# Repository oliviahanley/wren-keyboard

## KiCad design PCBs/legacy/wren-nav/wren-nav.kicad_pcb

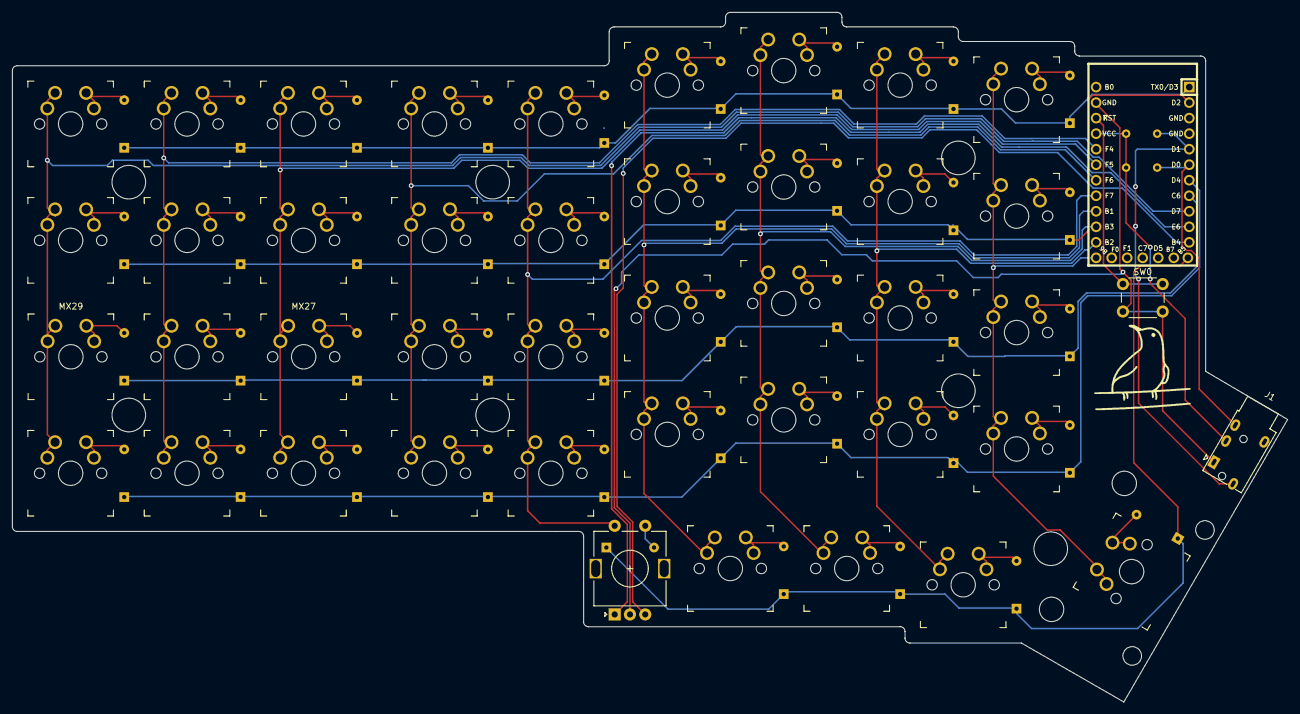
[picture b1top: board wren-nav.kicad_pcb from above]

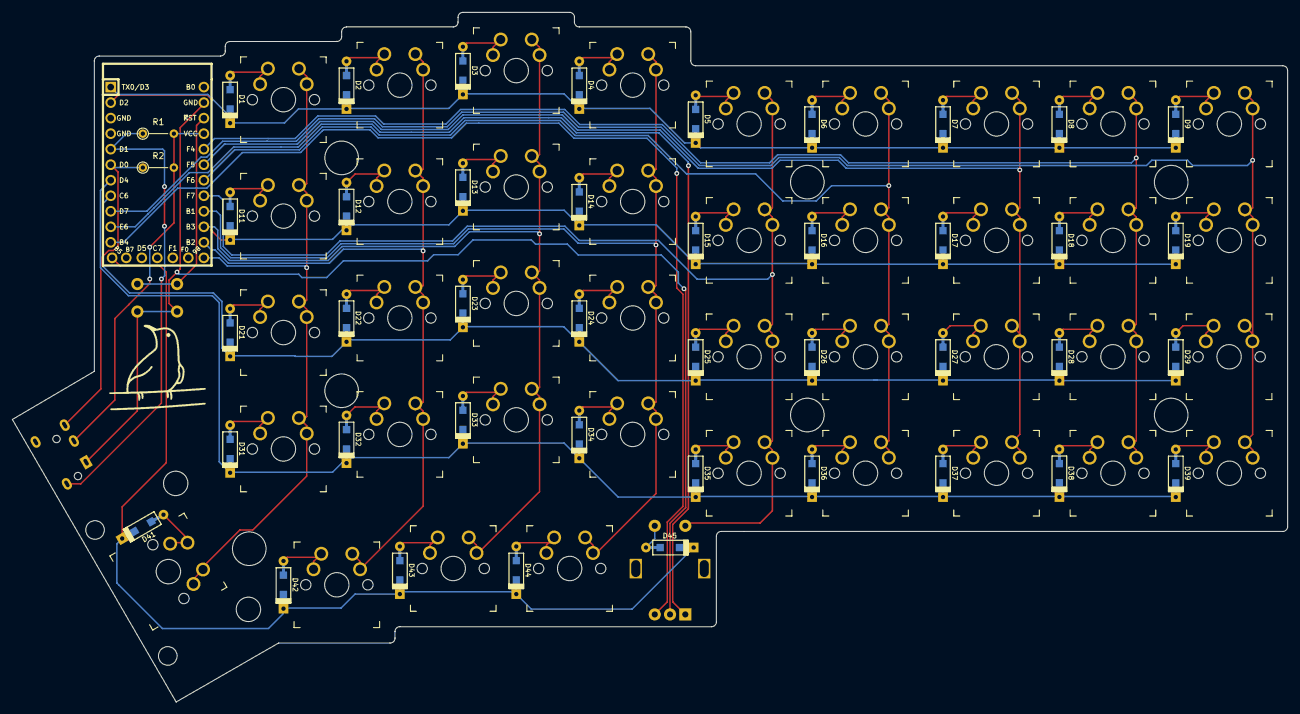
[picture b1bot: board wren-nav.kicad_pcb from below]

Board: 2 copper layers, 208.7 x 112.8 mm, 94 parts (44 on the bottom side), 62 nets.

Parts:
D1, D2, D3, D4, D5, D6, D7, D8, D9, D11, D12, D13, D14, D15, D16, D17, D18, D19, D21, D22, D23, D24, D25, D26, D27, D28, D29, D31, D32, D33, D34, D35, D36, D37, D38, D39, D41, D42, D43, D44, D45: D_Small; D_SOD123_axial
ENC1: Rotary_Encoder_Switch; RotaryEncoder_Alps_EC11E-Switch_Vertical_H20mm
H1, H2, H3, H4, H5, H6, H7: MountingHole; MountingHole_5.5mm
J1: TRRS_Jack; Jack_3.5mm_PJ320E_Horizontal
MX1, MX2, MX3, MX4, MX5, MX6, MX7, MX8, MX9, MX11, MX12, MX13, MX14, MX15, MX16, MX17, MX18, MX19, MX21, MX22, MX23, MX24, MX25, MX26, MX27, MX28, MX29, MX31, MX32, MX33, MX34, MX35, MX36, MX37, MX38, MX39, MX41, MX42, MX43, MX44: MX-NoLED; SW_MX_reversible
R1: 2.2kOhms; R_Axial_DIN0204_L3.6mm_D1.6mm_P5.08mm_Vertical
R2: 10kOhms; R_Axial_DIN0204_L3.6mm_D1.6mm_P5.08mm_Vertical
SW0: Reset; SW_PUSH_6mm
U1: Elite-C

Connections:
COL0: MX1.1, MX11.1, MX21.1, MX31.1, MX41.1, U1.13
COL1: MX2.1, MX12.1, MX22.1, MX32.1, MX42.1, U1.14
COL2: MX3.1, MX13.1, MX23.1, MX33.1, MX43.1, U1.15
COL3: MX4.1, MX14.1, MX24.1, MX34.1, MX44.1, U1.16
COL4: ENC1.S2, MX5.1, MX15.1, MX25.1, MX35.1, U1.17
COL5: MX6.1, MX16.1, MX26.1, MX36.1, U1.18
COL6: MX7.1, MX17.1, MX27.1, MX37.1, U1.19
COL7: MX8.1, MX18.1, MX28.1, MX38.1, U1.20
COL8: MX9.1, MX19.1, MX29.1, MX39.1, U1.9
ENC1-IN: D45.2, ENC1.S1
GND: ENC1.C, J1.T, SW0.2, U1.3, U1.4, U1.23
LEFT: ENC1.A, U1.10
unnamed: D1.2, MX1.2
unnamed: D2.2, MX2.2
unnamed: D3.2, MX3.2
unnamed: D4.2, MX4.2
unnamed: D5.2, MX5.2
unnamed: D6.2, MX6.2
unnamed: D7.2, MX7.2
unnamed: D8.2, MX8.2
unnamed: D9.2, MX9.2
unnamed: D11.2, MX11.2
unnamed: D12.2, MX12.2
unnamed: D13.2, MX13.2
unnamed: D14.2, MX14.2
unnamed: D15.2, MX15.2
unnamed: D16.2, MX16.2
unnamed: D17.2, MX17.2
unnamed: D18.2, MX18.2
unnamed: D19.2, MX19.2
unnamed: D21.2, MX21.2
unnamed: D22.2, MX22.2
unnamed: D23.2, MX23.2
unnamed: D24.2, MX24.2
unnamed: D25.2, MX25.2
unnamed: D26.2, MX26.2
unnamed: D27.2, MX27.2
unnamed: D28.2, MX28.2
unnamed: D29.2, MX29.2
unnamed: D31.2, MX31.2
unnamed: D32.2, MX32.2
unnamed: D33.2, MX33.2
unnamed: D34.2, MX34.2
unnamed: D35.2, MX35.2
unnamed: D36.2, MX36.2
unnamed: D37.2, MX37.2
unnamed: D38.2, MX38.2
unnamed: D39.2, MX39.2
unnamed: D41.2, MX41.2
unnamed: D42.2, MX42.2
unnamed: D43.2, MX43.2
unnamed: D44.2, MX44.2
unnamed: SW0.1, U1.22
RIGHT: ENC1.B, U1.11
ROW0: D1.1, D2.1, D3.1, D4.1, D5.1, D6.1, D7.1, D8.1, D9.1, U1.1
ROW1: D11.1, D12.1, D13.1, D14.1, D15.1, D16.1, D17.1, D18.1, D19.1, U1.2
ROW2: D21.1, D22.1, D23.1, D24.1, D25.1, D26.1, D27.1, D28.1, D29.1, U1.8
ROW3: D31.1, D32.1, D33.1, D34.1, D35.1, D36.1, D37.1, D38.1, D39.1, U1.7
ROW4: D41.1, D42.1, D43.1, D44.1, D45.1, U1.12
SCL: J1.R2, R2.1, U1.6
SDA: J1.S, R1.1, U1.5
VCC: J1.R1, R1.2, R2.2, U1.21
